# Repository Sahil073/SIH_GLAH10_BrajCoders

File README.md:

# Sanjeevni: Offline Wearable Telemetry & Edge AI Companion

[-green.svg>)](#)

[-cyan.svg>)](#)

Sanjeevni is an offline-first wearable telemetry system and on-device health safety companion. Designed for industrial workers, underground miners, high-altitude workers, and remote patients, it continuously captures physiological and environmental vitals via a multi-sensor ESP32 wearable and streams them over Bluetooth Low Energy (BLE) to an Android smartphone.

All biomedical signal processing, Pan-Tompkins QRS detection, motion classification, heat-stress modeling, and risk scoring execute locally on the mobile device CPU. No internet connection, cellular data, or external cloud infrastructure is required.

---

## System Architecture & Data Pipeline

---

## Repository Structure

```text
SIH_GLAH10_BrajCoders/
├── Hardware/                          # Firmware, testing sketches, PCB and hardware docs
│   ├── Device-Testing/                # 2-Tier component verification suite
│   │   ├── ADXL345/                   # Standalone I2C accelerometer serial test
│   │   ├── ADXL_Bluetooth/            # BLE stream test for ADXL345 (25 Hz)
│   │   ├── Bioamp_EXG/                # Standalone biopotential ADC serial test
│   │   ├── Bioamp_EXG_Bluetooth/      # BLE stream test for BioAmp EXG (500 Hz, 128-sample)
│   │   ├── Bluetooth/                 # BLE NUS loopback echo test
│   │   ├── DHT11/                     # Standalone digital temperature/humidity test
│   │   ├── DHT_Bluetooth/             # BLE stream test for DHT11 (0.5 Hz)
│   │   ├── LED/                       # GPIO and ESP32 clock sanity check
│   │   ├── MQ135/                     # Standalone hazardous gas ADC serial test
│   │   ├── MQ135_Bluetooth/           # BLE stream test for MQ135 (1 Hz)
│   │   ├── Moisture/                  # Standalone moisture ADC serial test
│   │   ├── Moisture_Bluetooth/        # BLE stream test for moisture sensor (0.5 Hz)
│   │   └── DEVICE_TESTING_GUIDE.md    # Modular hardware verification instructions
│   ├── ESP32_Sensor_Hub/              # Production multi-sensor BLE firmware
│   │   └── ESP32_Sensor_Hub.ino       # Full FreeRTOS multi-rate scheduler
│   ├── Sanjeevni_PCB/                 # Custom KiCad PCB files & manufacturing guide
│   │   ├── Sanjeevni_PCB.kicad_sch    # Schematic design
│   │   ├── Sanjeevni_PCB.kicad_pcb    # 2-layer PCB layout
│   │   ├── PCB schema.pdf             # Exported schematic reference
│   │   ├── PCB design.pdf             # Exported board layout reference
│   │   ├── PCB_Schematic.pdf          # Exported schematic reference
│   │   ├── PCB_Design.pdf             # Exported board layout reference
│   │   ├── PCB_Design_Guide.md        # Comprehensive electrical BOM and layout notes
│   │   ├── README.md                  # PCB subsystem overview and stackup
│   │   └── images/                    # 3D board renders
│   ├── HARDWARE_DOCS.md               # Pinouts, electrical specifications and BLE format
│   ├── README.md                      # Hardware overview and getting started guide
│   └── sample_data.txt                # 1,130 lines of verified field telemetry
│
├── docs/                              # Project specifications and hackathon decks
│   ├── images/                        # Research-style architecture and system diagrams
│   ├── BrajCoder's_SIH_Round1.pdf     # Smart India Hackathon Round 1 presentation
│   ├── BrajCoders_SIH_Round1.pdf      # Smart India Hackathon Round 1 presentation
│   ├── BrajCoders_SIH_2026.pdf        # SIH project submission & architectural slides
│   ├── sanjeevni_app_spec.pdf         # Mobile application technical specification
│   ├── sanjeevni_buildguide.pdf       # Hardware assembly and prototyping guide
│   └── DOCS_GUIDE.md                  # Index and overview of project documents
│
├── mobile-app/                        # React Native + Expo mobile application
│   ├── ai-engine/                     # On-device biomedical DSP and decision pipeline
│   │   ├── baseline/                  # Welford's online running baseline engine
│   │   ├── buffers/                   # High-performance RingBuffer
│   │   ├── decision/                  # Multi-window false-alarm gate & risk rules
│   │   ├── ecg/                       # Biquad IIR filters, Pan-Tompkins, HR & HRV
│   │   ├── environment/               # NWS Rothfusz heat index & AQI classifier
│   │   ├── fusion/                    # Multi-modal cross-sensor risk fusion
│   │   ├── mock/                      # Synthetic telemetry generator for simulator mode
│   │   ├── motion/                    # Dynamic activity state & 3-stage fall FSM
│   │   ├── __tests__/                 # Automated 7-test AI pipeline test suite
│   │   ├── index.ts                   # processSensorTick() main entrypoint
│   │   ├── types.ts                   # Strict data contracts for all sensor inputs
│   │   └── README.md                  # Comprehensive mathematical specification
│   ├── databaseConnections/           # On-device SQLite persistence layer
│   │   ├── database.ts                # Schema v4 table definitions, CRUD & pruning
│   │   ├── database.web.ts            # Web-safe mock fallback for browsers
│   │   ├── __tests__/                 # Automated 12-test database test suite
│   │   └── README.md                  # Table schemas, indices & retention policy
│   ├── src/                           # Mobile frontend source code
│   │   ├── app/                       # Expo Router tab layouts and navigation screens
│   │   │   ├── (auth)/                # Sign-in and sign-up flows (Clerk auth)
│   │   │   ├── (tabs)/                # Dashboard, Alerts, History, SOS, Profile
│   │   │   ├── _layout.tsx            # App initialization, providers & DB/AI bridge
│   │   │   └── connect-device.tsx     # BLE device discovery and pairing screen
│   │   ├── ble/                       # BLE Central manager, reassembly & reactive store
│   │   ├── components/                # Reusable UI widgets, sparklines, modals
│   │   ├── database/                  # On-device SQLite persistence layer (Schema v4)
│   │   │   ├── index.ts               # Public API wrapper & multi-user queries
│   │   │   ├── database.ts            # Schema definitions, CRUD & retention pruning
│   │   │   ├── database.web.ts        # Web-safe mock fallback for browsers
│   │   │   ├── vitalsHistory.ts       # Time-series vitals history query service
│   │   │   ├── __tests__/             # Automated 12-test database test suite
│   │   │   └── README.md              # Table schemas, indices & retention policy
│   │   ├── hooks/                     # Custom hooks (useDashboardData, useBle, useAiRisk)
│   │   └── services/                  # aiBridge.ts (BLE -> AI Pipeline -> SQLite)
│   ├── __tests__/                     # End-to-end hardware-to-UI integration test
│   ├── app.json                       # Expo configuration, Android permissions & plugins
│   ├── eas.json                       # Standalone APK build profile (arm64-v8a)
│   ├── package.json                   # Mobile dependencies and npm scripts
│   └── README.md                      # Mobile subsystem documentation
│
├── package.json                       # Root developer convenience test scripts
└── README.md                          # Project documentation and run guide
```

---

## Hardware Setup & Firmware Flashing

### 1. Prerequisites

- **Arduino IDE**: Version 2.x ([Download Arduino IDE](https://www.arduino.cc/en/software))
- **ESP32 Board Package**: Install `esp32` by Espressif via `Boards Manager`
- **Required Libraries** (via `Tools > Manage Libraries...`):
  - `Adafruit ADXL345`
  - `Adafruit Unified Sensor`
  - `DHT sensor library` (by Adafruit)
  - `ArduinoJson` (by Benoit Blanchon, v6.x or v7.x)

### 2. Sensor Pinout Mapping

| Sensor Module       | Physical Interface | ESP32 GPIO                         | Operating Voltage           | Notes                                        |
| :------------------ | :----------------- | :--------------------------------- | :-------------------------- | :------------------------------------------- |
| **BioAmp EXG Pill** | Analog Voltage     | `GPIO 34`                          | 3.3V                        | ADC1_CH6 (Input-only, 500 Hz sampling)       |
| **ADXL345**         | I2C                | `GPIO 21` (SDA)<br>`GPIO 22` (SCL) | 3.3V                        | I2C Address `0x53` (SDO to GND)              |
| **DHT11**           | Proprietary 1-Wire | `GPIO 4`                           | 3.3V / 5V                   | Digital I/O (10 kΩ pull-up required if bare) |
| **MQ135**           | Analog Voltage     | `GPIO 35`                          | 5.0V (Heater)<br>3.3V (ADC) | ADC1_CH7 (Input-only, heater requires 5V)    |
| **Moisture Sensor** | Analog Voltage     | `GPIO 32`                          | 3.3V                        | ADC1_CH4 (Supports digital and analog)       |

> **Critical ADC Note:** Only ADC1 pins are used. ADC2 pins (`GPIO 0, 2, 4, 12, 13, 14, 15, 25, 26, 27`) cannot be used for analog reads when Bluetooth or Wi-Fi is active.

### 3. Flashing the Sensor Hub Firmware

1. Connect your ESP32 Dev Module via micro-USB.
2. In Arduino IDE, select:
   - **Board**: `ESP32 Dev Module`
   - **Upload Speed**: `921600`
   - **Flash Frequency**: `80MHz`
   - **Port**: Select your active COM port.
3. Open [`Hardware/ESP32_Sensor_Hub/ESP32_Sensor_Hub.ino`](Hardware/ESP32_Sensor_Hub/ESP32_Sensor_Hub.ino).
4. Click **Upload**.
5. Once uploaded, open the Serial Monitor at `115200 baud`. The ESP32 will initialize all sensors and start advertising over BLE as **`ESP32_SENSOR_HUB_BLE`**.

---

## Mobile App Setup & Execution

### 1. Prerequisites

- **Node.js**: v18.x or v20.x LTS ([Download Node.js](https://nodejs.org))
- **npm**: v9.x or higher
- **Physical Android Phone**: Bluetooth 4.2+ and Location enabled (for native BLE testing).

### 2. Installation & Configuration

```bash
# 1. Navigate to the mobile app directory
cd mobile-app

# 2. Copy the sample environment file
cp .env.example .env

# 3. Install dependencies
npm install --legacy-peer-deps
```

### 3. Running in Development

#### Option A: Expo Go (Simulation Mode)

```bash
npm start
```

- Scan the displayed QR code with the **Expo Go** application on Android.
- Because native BLE binary drivers are unavailable inside Expo Go, Sanjeevni automatically engages its built-in mathematical synthetic generator (`syntheticDataGenerator.ts`). It generates realistic 500 Hz ECG waveforms, accelerometer tilts, and ambient thermal cycles for full UI testing.

#### Option B: Standalone Android APK (Physical BLE Mode)

To connect to the physical ESP32 hardware, compile an installable standalone `.apk`:

```bash
# Via EAS Cloud Build:
npm install -g eas-cli
npx eas login
npx eas build -p android --profile preview

# Or compile locally with Gradle:
npx expo prebuild --platform android
cd android
./gradlew assembleRelease -PreactNativeArchitectures=arm64-v8a
```

Install the resulting `.apk` on your phone, enable Bluetooth, power on the ESP32, and launch Sanjeevni. The app will pair and start streaming telemetry without internet or Wi-Fi.

---

## Automated Verification & Test Suites

The project includes unit and integration tests across the entire stack. Run them from the workspace root:

### Run All Test Suites:

```bash
npm test
```

### Run Individual Test Suites:

1. **On-Device AI Engine Test Suite** (`7/7 Passed`):

   ```bash
   npm run test:ai
   ```

   - Test 1: Biquad IIR Bandpass (0.5–40 Hz) & 50 Hz Notch filter attenuation.
   - Test 2: Pan-Tompkins QRS peak detection and RR interval validation.
   - Test 3: Mathematical derivation of BPM, RMSSD, and SDNN.
   - Test 4: Dynamic motion classification and 3-stage fall detection FSM.
   - Test 5: Environmental Heat Index calculation against NOAA benchmark tables.
   - Test 6: Full end-to-end `processSensorTick()` pipeline orchestration.
   - Test 7: Multi-window emergency alarm and false-alarm gate trigger logic.

2. **SQLite Database & Schema Test Suite** (`12/12 Passed`):

   ```bash
   npm run test:db
   ```

   - Test 1: Schema creation, tables (`readings`, `alerts`, `user_profile`, `rolling_baseline`), and indices.
   - Test 2: Readings insertion and query operations.
   - Test 3: Alerts table insertion and severity enum check constraint (`LOW`, `MODERATE`, `HIGH`, `CRITICAL`).
   - Test 4: Single-profile configuration constraint.
   - Test 5: Rolling baseline upsert via `ON CONFLICT DO UPDATE`.
   - Test 6: Automated 7-day circular data pruning.
   - Test 7: Sensor aggregate statistics calculations.
   - Test 8: Historical sensor queries with timestamp ordering and pagination limits.
   - Test 9: Alert deletion and bulk clear operations.
   - Test 10: Rich user profile persistence and local session management.
   - Test 11: Multi-user data isolation and tenant partitioning.
   - Test 12: 6-month historical data rollup downsampling and user erasure utility.

3. **End-to-End System Integration Test**:

   ```bash
   npm run test:e2e
   ```

   - Step 1: Parses raw multi-chunk ESP32 Nordic UART BLE packets.
   - Step 2: Executes the sliding-window AI pipeline.
   - Step 3: Verifies persistent storage in the local SQLite database.

4. **TypeScript Type Checking**:
   ```bash
   npm run typecheck
   ```

   - Validates TypeScript types across the entire mobile codebase (0 errors).

---

## BLE Protocol Reference (Nordic UART Service)

The ESP32 communicates using the Nordic UART Service (NUS):

| Identifier                     | UUID Value                             |
| :----------------------------- | :------------------------------------- |
| **Service UUID**               | `6E400001-B5A3-F393-E0A9-E50E24DCCA9E` |
| **RX Characteristic (Write)**  | `6E400002-B5A3-F393-E0A9-E50E24DCCA9E` |
| **TX Characteristic (Notify)** | `6E400003-B5A3-F393-E0A9-E50E24DCCA9E` |

### Telemetry Packet Payloads (Newline Delimited `\n`)

- **BioAmp EXG (Sensor ID 1)**:
  `{"v":1,"sensor":1,"seq":104,"rate":500,"samples":[2048,2060,2090,...],"ts":181482}\n`
- **ADXL345 (Sensor ID 2)**:
  `{"v":1,"sensor":2,"seq":4518,"data":{"x":0.15,"y":-0.22,"z":9.81},"ts":181483}\n`
- **DHT11 (Sensor ID 3)**:
  `{"v":1,"sensor":3,"seq":120,"data":{"temperature":32.5,"humidity":68.0},"ts":181500}\n`
- **MQ135 (Sensor ID 4)**:
  `{"v":1,"sensor":4,"seq":180,"data":{"raw":480},"ts":181751}\n`
- **Moisture Sensor (Sensor ID 5)**:
  `{"v":1,"sensor":5,"seq":95,"data":{"raw":520},"ts":181800}\n`

---

## Offline Privacy & Data Integrity

- **Zero Cloud Transmission**: All ECG analysis, Pan-Tompkins QRS detection, and environmental evaluations execute on the smartphone CPU. No biometric data leaves the device.
- **Local SQLite Retention**: Telemetry and safety alerts are stored in an encrypted/sandboxed local SQLite database (`sanjeevni.db`) with an automated 7-day circular pruning policy to preserve phone storage.
- **Credential Protection**: Environment files and keys are excluded via `.gitignore`.

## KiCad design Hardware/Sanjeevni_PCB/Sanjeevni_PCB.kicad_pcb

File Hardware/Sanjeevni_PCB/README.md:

# Sanjeevni Custom Wearable PCB

This directory contains the schematic design, printed circuit board (PCB) layout, 3D renderings, and manufacturing guidelines for the Sanjeevni wearable hardware prototype, designed using KiCad.

---

## Directory Contents

| File / Folder | Type | Description |
| :--- | :--- | :--- |
| [`Sanjeevni_PCB.kicad_sch`](Sanjeevni_PCB.kicad_sch) | KiCad Schematic | Full schematic capture including power regulation, ESP32 core, sensor front-ends, and programming pads. |
| [`Sanjeevni_PCB.kicad_pcb`](Sanjeevni_PCB.kicad_pcb) | KiCad Board Layout | 2-layer PCB layout routing power planes, high-frequency digital lines, and shielded analog tracks. |
| [`Sanjeevni_PCB.kicad_pro`](Sanjeevni_PCB.kicad_pro) | Project File | KiCad project configuration and library mappings. |
| [`PCB schema.pdf`](<PCB schema.pdf>) | Schematic Export | High-resolution PDF export of the complete circuit schematic for easy review without KiCad installed. |
| [`PCB design.pdf`](<PCB design.pdf>) | Layout Export | High-resolution PDF export of the top and bottom copper layers, silkscreen, and drill guides. |
| [`PCB_Schematic.pdf`](PCB_Schematic.pdf) | Schematic Export | High-resolution PDF export of the complete circuit schematic for easy review without KiCad installed. |
| [`PCB_Design.pdf`](PCB_Design.pdf) | Layout Export | High-resolution PDF export of the top and bottom copper layers, silkscreen, and drill guides. |
| [`PCB_Design_Guide.md`](PCB_Design_Guide.md) | Engineering Guide | In-depth documentation detailing the Bill of Materials (BOM), trace width calculations, noise isolation, and step-by-step routing methodology. |
| [`images/`](images/) | 3D Visualizations | Rendered views of the populated board: [top view](images/top%20view.png), [isometric view 1](images/isometric%20view.png), [isometric view 2](images/isometric%20view%202.png). |
| [`images/`](images/) | 3D Visualizations | Rendered views of the populated board: [top view](images/top_view.png), [isometric view 1](images/isometric_view_1.png), [isometric view 2](images/isometric_view_2.png). |

---

## Hardware Architecture & Design Decisions

### 1. Form Factor & Enclosure Considerations
- **Field-Sealed Wearable**: To ensure durability in harsh industrial or remote environments, the production board does not include an onboard micro-USB or Type-C port. 
- **Factory Programming Interface**: 6 exposed test pads (`GND`, `3V3`, `TX`, `RX`, `EN`, `IO0`) are positioned along the board edge, allowing firmware programming via a removable pogo-pin jig before sealing.
- **Power Connection**: 2-pin JST-PH 2.00 mm horizontal receptacle for standard 3.7V single-cell LiPo rechargeable batteries.

### 2. Sensor Integration Strategy
- **BioAmp EXG Pill (Daughterboard)**: Mounted via standard 2.54 mm female pin headers rather than integrating bare IC components. This isolates the sensitive biopotential instrumentation amplifier (110 dB CMRR, 4th-order active bandpass filter) from digital switching noise and RF ground bounce.
- **ADXL345 (Bare IC)**: Direct LGA-14 surface mount footprint on the I2C bus (`GPIO 21` SDA, `GPIO 22` SCL) with 4.7 kΩ pull-up resistors and local 100 nF decoupling.
- **DHT11 (Through-Hole Footprint)**: 4-pin single-row connector with pull-up resistor on the single-wire data line (`GPIO 4`).
- **MQ135 (Raw Element)**: 6-pin circular footprint for the bare electrochemical gas sensing element. Driven by an onboard MT3608 boost converter providing the required 5V rail for the internal heating element.

### 3. Power Distribution Architecture
- **Battery Input**: 3.7V nominal LiPo (operating range 3.0V – 4.2V).
- **3.3V Logic Rail**: AMS1117-3.3 low-dropout linear regulator providing clean 3.3V power to the ESP32-WROOM-32D module, ADXL345, DHT11, and BioAmp EXG Pill. Bulk decoupling capacitors (10 µF tantalum + 100 nF ceramic) are placed directly at the regulator and MCU pins.
- **5.0V Heater Rail**: MT3608 DC-DC step-up switching regulator stepping 3.7V up to 5.0V dedicated exclusively to the MQ135 heating coil. Thermal relief vias and a dedicated ground return keep switching noise out of the analog measurement circuits.

---

## Fabrication Specifications

- **Layer Count**: 2 Layers (Top Layer: Signal & Power, Bottom Layer: Unbroken Ground Plane)
- **Board Material**: Standard FR-4
- **Finished Copper Weight**: 1 oz (35 µm)
- **Dielectric Thickness**: 1.6 mm
- **Minimum Trace Width**: 0.25 mm (10 mil) for signal traces; 0.6 mm (24 mil) for 3.3V power distribution
- **Minimum Clearance**: 0.2 mm (8 mil)
- **Minimum Drill Hole Size**: 0.3 mm (via), 0.9 mm (through-hole component pins)

For the complete component catalog, KiCad symbol mappings, and step-by-step routing layout instructions, consult [`PCB_Design_Guide.md`](PCB_Design_Guide.md).

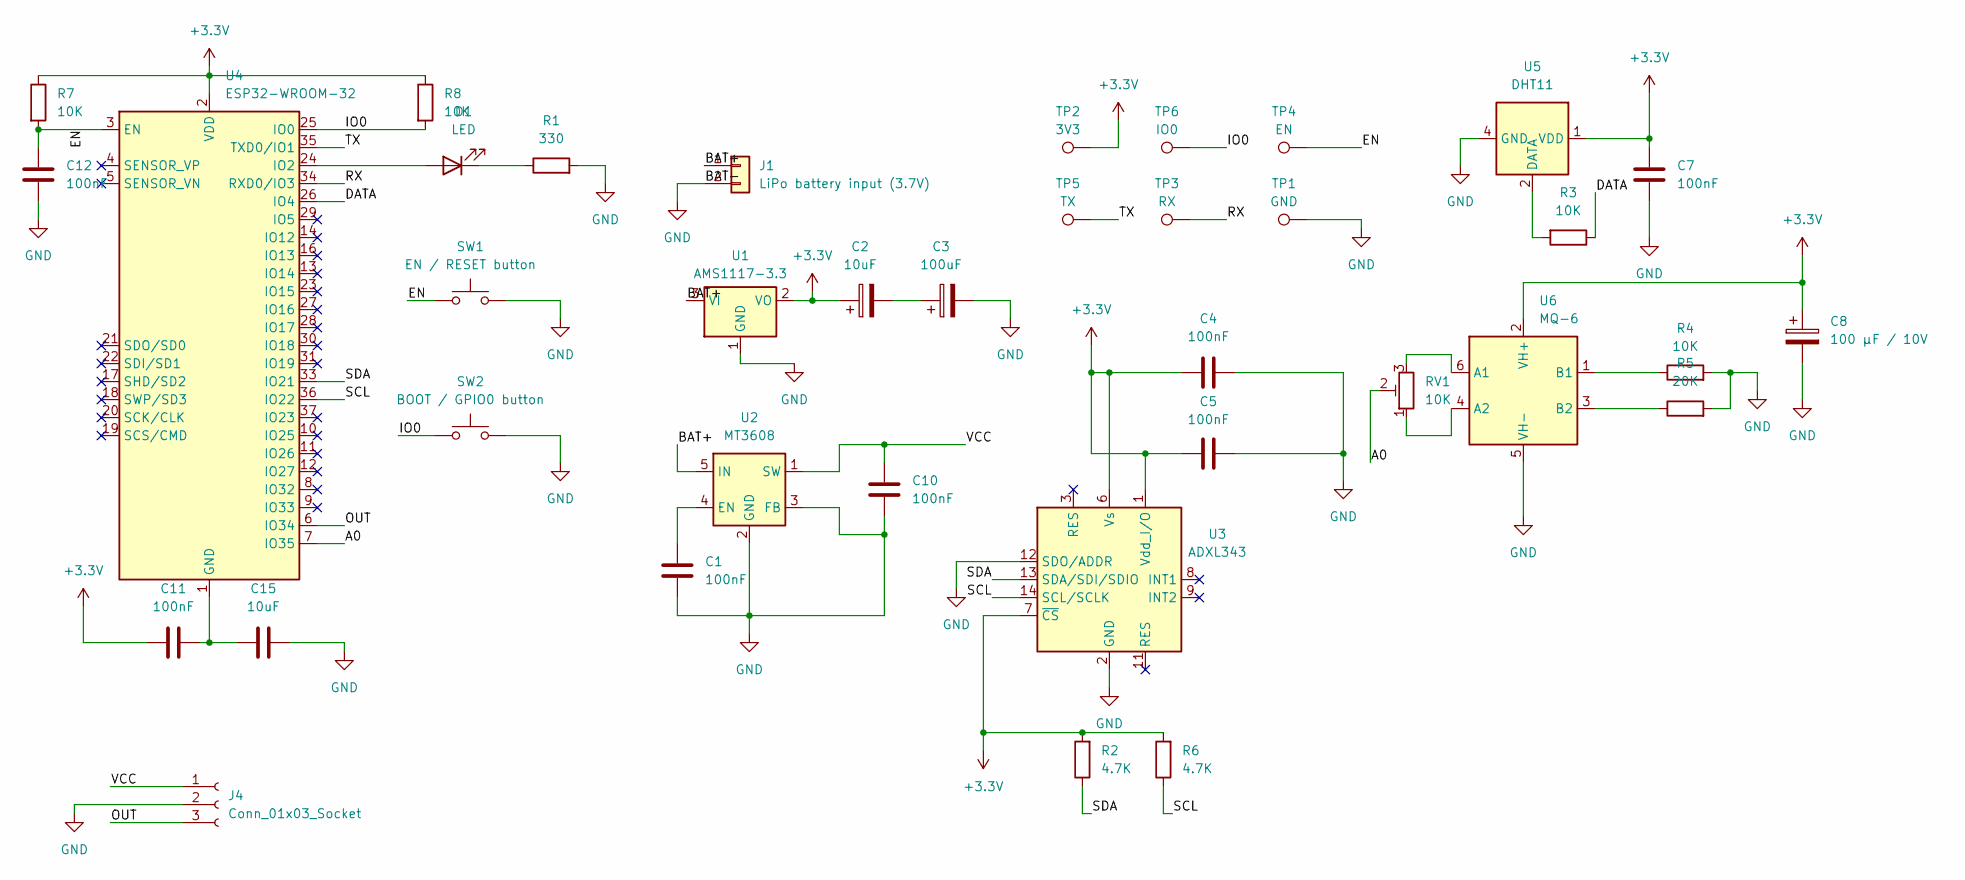
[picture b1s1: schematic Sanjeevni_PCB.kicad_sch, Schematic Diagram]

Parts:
C1, C4, C5, C7, C10, C11, C12: 100nF; C_0402_1005Metric
C2: 10uF; C_0805_2012Metric
C3: 100uF; C_0805_2012Metric
C8: 100 µF / 10V; C_0805_2012Metric
C15: 10uF; C_0402_1005Metric
D1: LED; LED_0402_1005Metric
J1: LiPo battery input (3.7V); JST_PH_S2B-PH-K_1x02_P2.00mm_Horizontal
J4: Conn_01x03_Socket; PinSocket_1x03_P2.00mm_Horizontal
R1: 330; R_0402_1005Metric
R2, R6: 4.7K; R_0402_1005Metric
R3, R4, R7, R8: 10K; R_0402_1005Metric
R5: 20K; R_0402_1005Metric
RV1: 10K; Potentiometer_Bourns_3296W_Vertical
SW1: EN / RESET button; SW_SPST_CK_RS282G05A3
SW2: BOOT / GPIO0 button; SW_SPST_CK_RS282G05A3
TP1: GND; TestPoint_Pad_1.5x1.5mm
TP2: 3V3; TestPoint_Pad_1.5x1.5mm
TP3: RX; TestPoint_Pad_1.5x1.5mm
TP4: EN; TestPoint_Pad_1.5x1.5mm
TP5: TX; TestPoint_Pad_1.5x1.5mm
TP6: IO0; TestPoint_Pad_1.5x1.5mm
U1: AMS1117-3.3; SOT-223-3_TabPin2
U2: MT3608; SOT-23-6
U3: ADXL343; LGA-14_3x5mm_P0.8mm_LayoutBorder1x6y
U4: ESP32-WROOM-32
U5: DHT11; Aosong_DHT11_5.5x12.0_P2.54mm
U6: MQ-6

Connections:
+3.3V: C2.1, C4.1, C5.1, C7.1, C8.1, C11.1, R2.2, R6.2, R7.1, R8.1, TP2.1 (1_1), U1.2 (VO), U3.1 (Vdd_I/O), U3.6 (Vs), U3.7 (~CS), U4.2 (VDD), U5.1 (VDD), U6.2 (VH+)
/A0: RV1.2, U4.7 (IO35)
/BAT+: J1.1, U1.3 (VI), U2.5 (IN)
/DATA: R3.1, U4.26 (IO4)
/EN: C12.1, R7.2, SW1.1, TP4.1 (1_1), U4.3 (EN)
/IO0: R8.2, SW2.1, TP6.1 (1_1), U4.25 (IO0)
/OUT: J4.3, U4.6 (IO34)
/RX: TP3.1 (1_1), U4.34 (RXD0/IO3)
/SCL: R6.1, U3.14 (SCL/SCLK), U4.36 (IO22)
/SDA: R2.1, U3.13 (SDA/SDI/SDIO), U4.33 (IO21)
/TX: TP5.1 (1_1), U4.35 (TXD0/IO1)
/VCC: C10.1, J4.1, U2.1 (SW)
GND: C1.2, C3.2, C4.2, C5.2, C7.2, C8.2, C10.2, C12.2, C15.2, J1.2, J4.2, R1.2, R4.2, R5.2, SW1.2, SW2.2, TP1.1 (1_1), U1.1 (GND), U2.2 (GND), U2.3 (FB), U3.2 (GND), U3.4 (GND), U3.5 (GND), U3.12 (SDO/ADDR), U5.4 (GND), U6.5 (VH-)
unnamed: C2.2, C3.1
unnamed: C11.2, C15.1, U4.1 (GND), U4.15 (GND), U4.38 (GND), U4.39 (GND)
unnamed: D1.2 (A), U4.24 (IO2)
unnamed: D1.1 (K), R1.1
unnamed: C1.1, U2.4 (EN)
unnamed: R3.2, U5.2 (DATA)
unnamed: RV1.3, U6.6 (A1)
unnamed: RV1.1, U6.4 (A2)
unnamed: R4.1, U6.1 (B1)
unnamed: R5.1, U6.3 (B2)

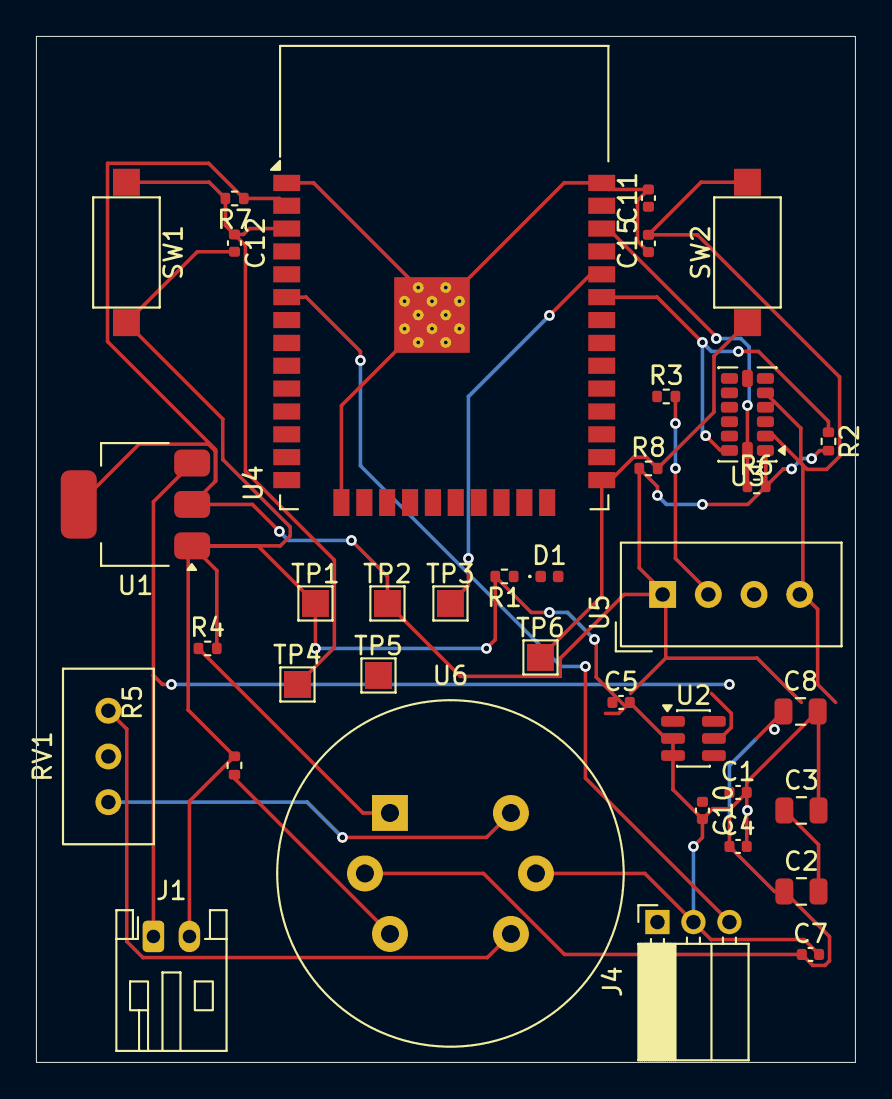
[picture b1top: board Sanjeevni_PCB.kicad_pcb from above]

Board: 2 copper layers, 45.5 x 57.0 mm, 37 parts (0 on the bottom side), 23 nets.
